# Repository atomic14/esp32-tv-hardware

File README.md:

# WIP - ESP32-TV Hardware Files

This is Work In Progress - I'm still working on this.

This repo contains/will contain the hardware design files for the ESP32-TV project.

## Schematic

You can either open this up in KiCad, or there's a PDF [here](./images/micro-esp32-s3.pdf).

## PCB

Open this up in KiCad to export the Gerber files.

## What's this all about?

More details to follow...

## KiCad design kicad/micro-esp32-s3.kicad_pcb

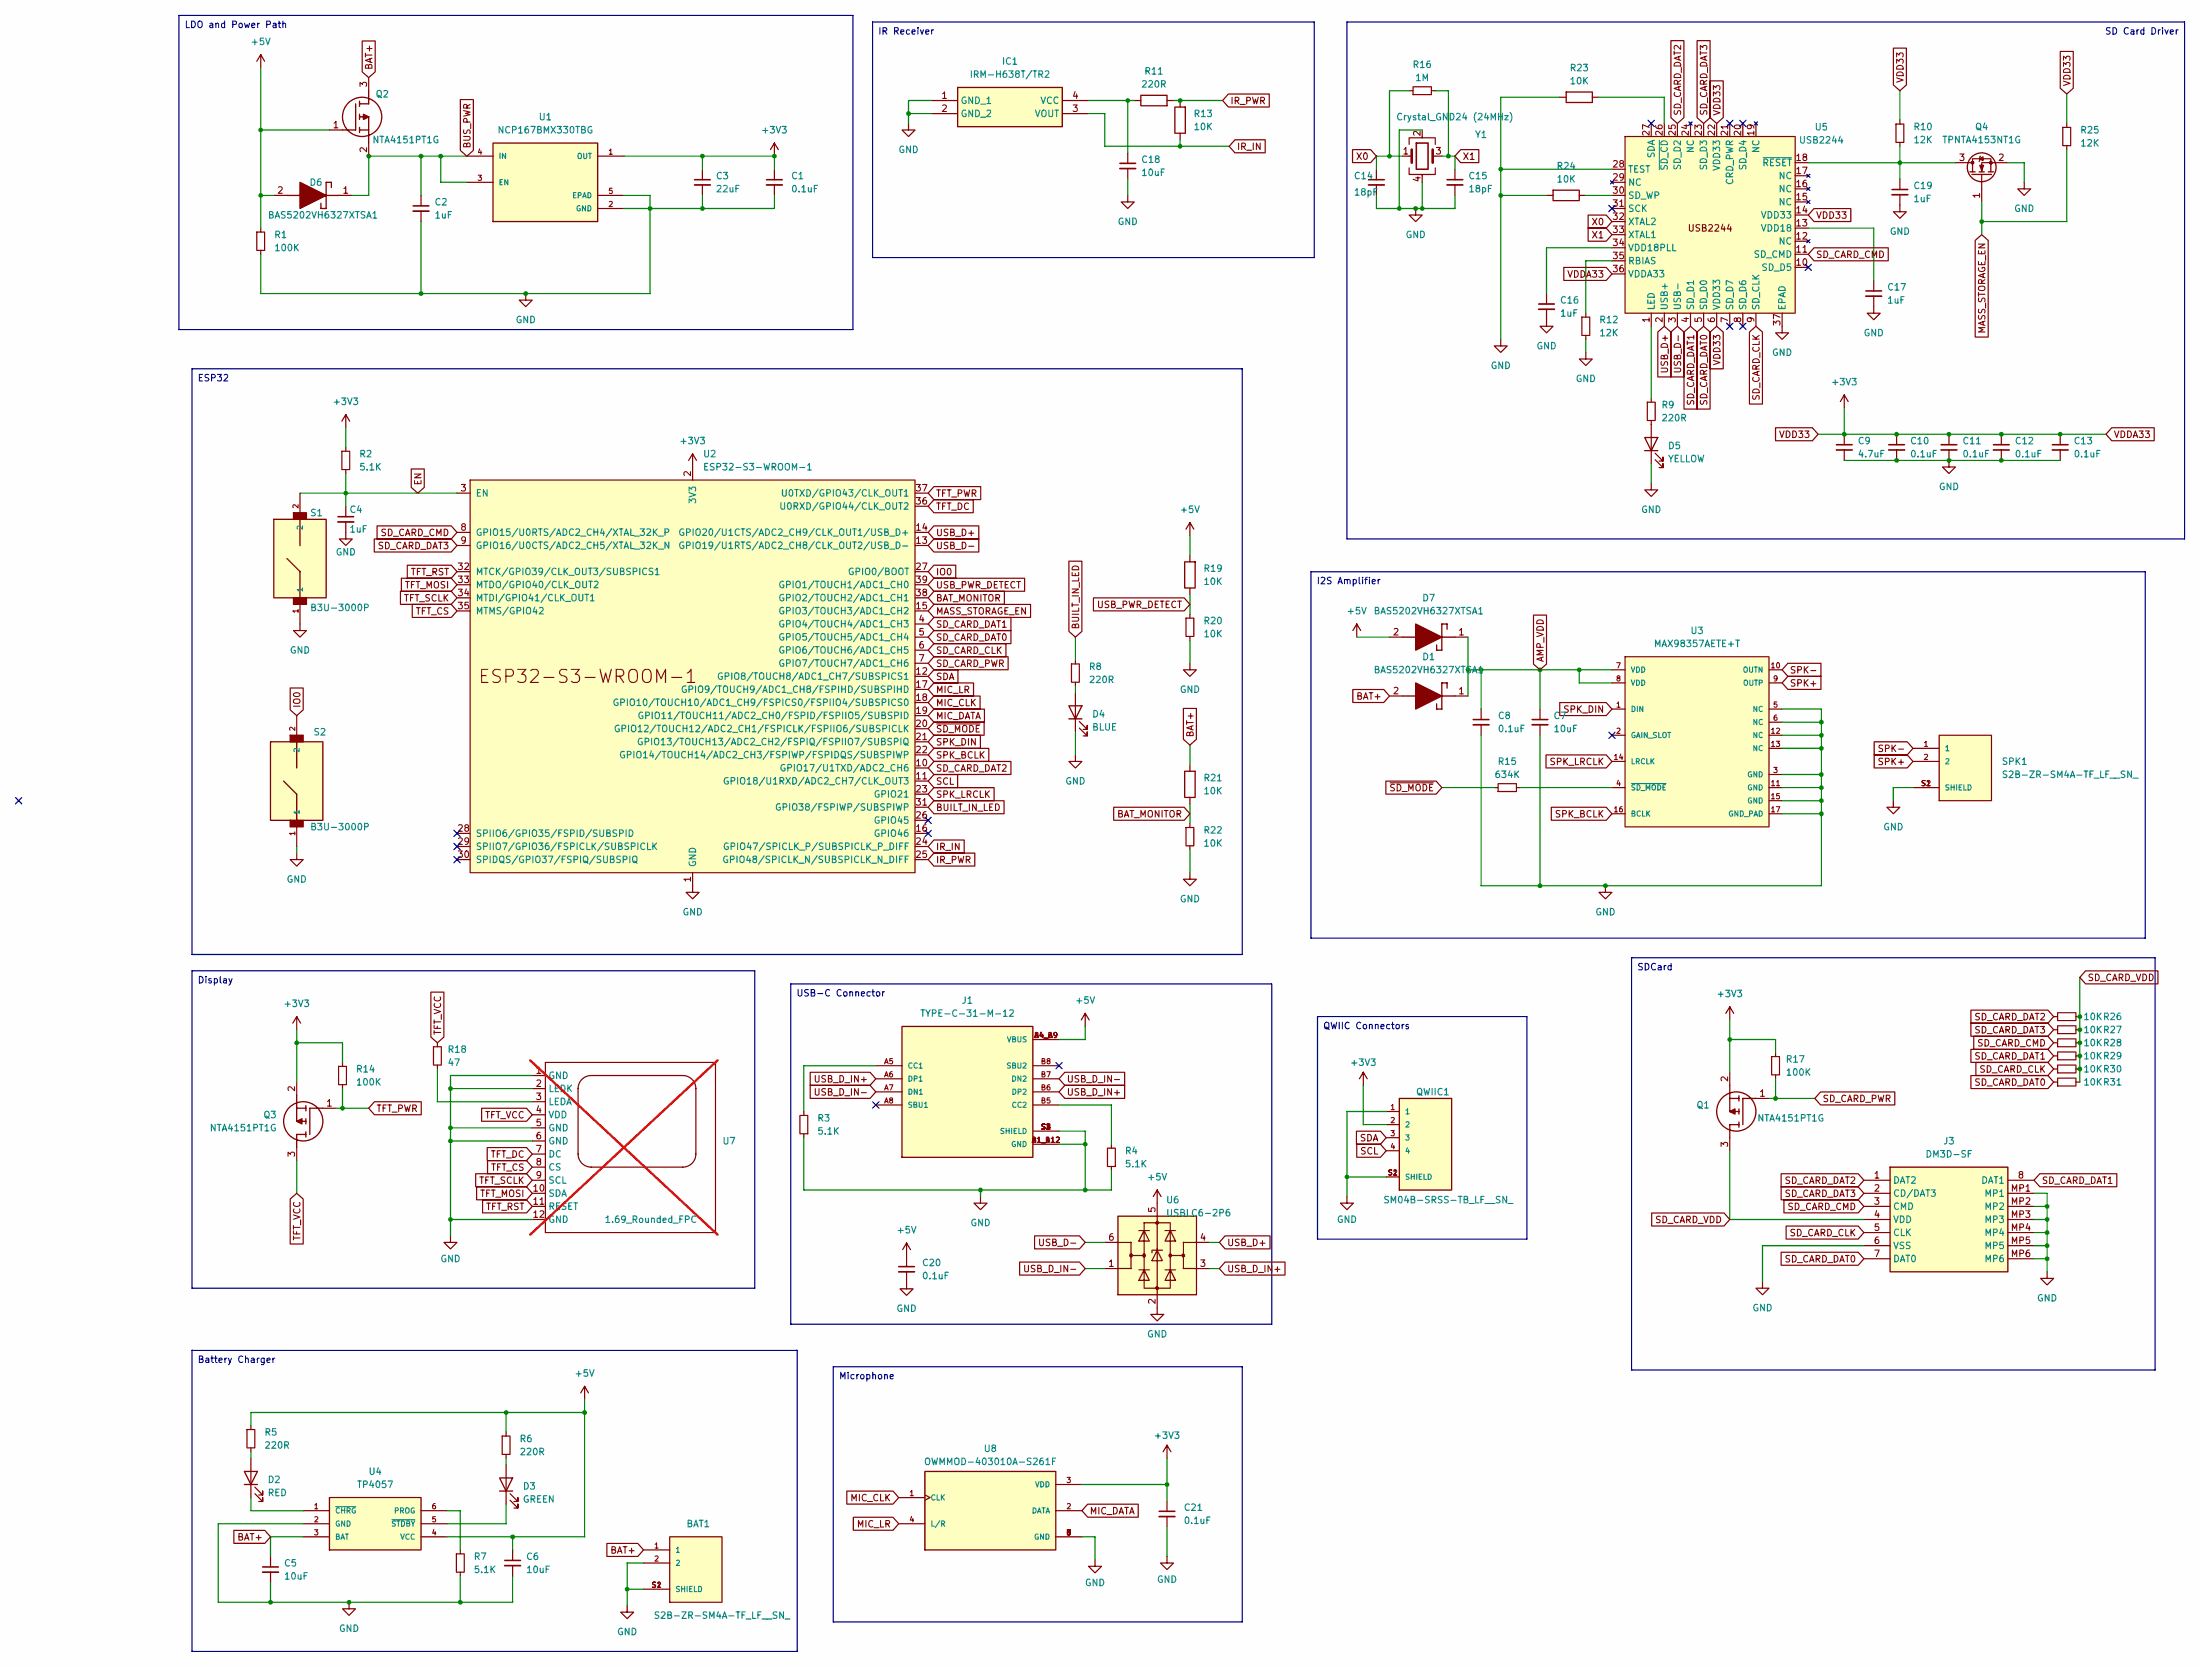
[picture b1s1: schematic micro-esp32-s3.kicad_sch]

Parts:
BAT1: S2B-ZR-SM4A-TF_LF__SN_; JST_S2B-ZR-SM4A-TF_LF__SN_; PARTREV N/A
C1, C8, C10, C11, C12, C13, C20, C21: 0.1uF; C_0402_1005Metric
C2: 1uF; C_0402_1005Metric; Mfg Part # test
C3: 22uF; C_0402_1005Metric
C4, C16, C17, C19: 1uF; C_0402_1005Metric
C5, C6, C7, C18: 10uF; C_0402_1005Metric
C9: 4.7uF; C_0402_1005Metric
C14, C15: 18pF; C_0402_1005Metric
D1, D6, D7: BAS5202VH6327XTSA1; SODFL1608X59N; Manufacturer_Part_Number BAS5202VH6327XTSA1; Mouser Part Number 726-BAS5202VH6327XTS
D2: RED; LED_0402_1005Metric
D3: GREEN; LED_0402_1005Metric
D4: BLUE; LED_0402_1005Metric
D5: YELLOW; LED_0402_1005Metric
IC1: IRM-H638T/TR2; SOP254P700X405-4N; Manufacturer_Part_Number IRM-H638M3/TR2
J1: TYPE-C-31-M-12; HRO_TYPE-C-31-M-12; PARTREV 2020.12.08
J3: DM3D-SF; DM3DSF; Manufacturer_Part_Number DM3D-SF; Mouser Part Number 798-DM3D-SF
Q1, Q2, Q3: NTA4151PT1G; SOT50P160X90-3N; Manufacturer_Part_Number NTA4151PT1G; Mouser Part Number 863-NTA4151PT1G
Q4: TPNTA4153NT1G; SOT-523
QWIIC1: SM04B-SRSS-TB_LF__SN_; JST_SM04B-SRSS-TB_LF__SN_
R1, R14, R17: 100K; R_0402_1005Metric
R2, R3, R4, R7: 5.1K; R_0402_1005Metric
R5, R6, R8, R9, R11: 220R; R_0402_1005Metric
R10, R12, R25: 12K; R_0402_1005Metric
R13, R19, R20, R21, R22, R23, R24, R26, R27, R28, R29, R30, R31: 10K; R_0402_1005Metric
R15: 634K; R_0402_1005Metric
R16: 1M; R_0402_1005Metric
R18: 47; R_0402_1005Metric
S1, S2: B3U-3000P; SW_B3U-3000P
SPK1: S2B-ZR-SM4A-TF_LF__SN_; JST_S2B-ZR-SM4A-TF_LF__SN_; PARTREV N/A
U1: NCP167BMX330TBG; VREG_NCP167BMX330TBG; PARTREV 5
U2: ESP32-S3-WROOM-1; ESP32-S3-WROOM-1U
U3: MAX98357AETE+T; Maxim_Electronics-21-0896-0-0-0; mouser part number 700-MAX98357AETE+T; digikey description Amplifier IC 2-Channel (Stereo) Class D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
U4: TP4057; SOT-23-6
U5: USB2244; QFN-36-1EP_6x6mm_P0.5mm_EP4.1x4.1mm
U6: USBLC6-2P6; SOT-666
U7: 1.69_Rounded_FPC; fpc_12_pin_0.7_pitch; not fitted
U8: OWMMOD-403010A-S261F; MIC_OWMMOD-403010A-S261F; PARTREV 00; DigiKey_Part_Number 3949-OWMMOD-403010A-S261F-ND
Y1: Crystal_GND24 (24MHz); Crystal_SMD_3225-4Pin_3.2x2.5mm

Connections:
+5V: C6.1, C20.1, D6.2 (A), D7.2 (A), J1.A4_B9 (VBUS), J1.B4_A9 (VBUS), Q2.1 (G), R1.1, R5.1, R6.1, R19.2, U4.4 (VCC), U6.5 (VBUS)
AMP_VDD: C7.1, C8.1, D1.1 (K), D7.1 (K), U3.7 (VDD), U3.8 (VDD)
BAT+: BAT1.1, C5.1, D1.2 (A), Q2.3 (D), R21.2, U4.3 (BAT)
BAT_MONITOR: R21.1, R22.1, U2.38 (GPIO2/TOUCH2/ADC1_CH1)
BUILT_IN_LED: R8.1, U2.31 (GPIO38/FSPIWP/SUBSPIWP)
BUS_PWR: C2.1, D6.1 (K), Q2.2 (S), U1.3 (EN), U1.4 (IN)
EN: C4.1, R2.2, S1.2, U2.3 (EN)
GND: BAT1.2, BAT1.S1 (SHIELD), BAT1.S2 (SHIELD), C1.2, C2.2, C3.2, C4.2, C5.2, C6.2, C7.2, C8.2, C9.2, C10.2, C11.2, C12.2, C13.2, C14.2, C15.2, C16.2, C17.2, C18.2, C19.2, C20.2, C21.2, D4.1 (K), D5.1 (K), IC1.1 (GND_1), IC1.2 (GND_2), J1.A1_B12 (GND), J1.B1_A12 (GND), J1.S1 (SHIELD), J1.S2 (SHIELD), J1.S3 (SHIELD), J1.S4 (SHIELD), J3.6 (VSS), J3.MP1, J3.MP2, J3.MP3, J3.MP4, J3.MP5, J3.MP6, Q4.2 (S), QWIIC1.1, QWIIC1.S1 (SHIELD), QWIIC1.S2 (SHIELD), R1.2, R3.1, R4.1, R7.2, R12.2, R20.2, R22.2, R23.2, R24.2, S1.1, S2.1, SPK1.S1 (SHIELD), SPK1.S2 (SHIELD), U1.2 (GND), U1.5 (EPAD), U2.1 (GND), U2.40 (GND), U2.41 (GND), U3.3 (GND), U3.5 (NC), U3.6 (NC), U3.11 (GND), U3.12 (NC), U3.13 (NC), U3.15 (GND), U3.17 (GND_PAD), U4.2 (GND), U5.28 (TEST), U5.37 (EPAD), U6.2 (GND), U7.1 (GND), U7.2 (LEDK), U7.5 (GND), U7.6 (GND), U7.12 (GND), U8.5 (GND), U8.6 (GND), U8.7 (GND), U8.8 (GND), Y1.2, Y1.4
IO0: S2.2, U2.27 (GPIO0/BOOT)
IR_IN: IC1.3 (VOUT), R13.1, U2.24 (GPIO47/SPICLK_P/SUBSPICLK_P_DIFF)
IR_PWR: R11.2, R13.2, U2.25 (GPIO48/SPICLK_N/SUBSPICLK_N_DIFF)
MASS_STORAGE_EN: Q4.1 (G), R25.2, U2.15 (GPIO3/TOUCH3/ADC1_CH2)
MIC_CLK: U2.18 (GPIO10/TOUCH10/ADC1_CH9/FSPICS0/FSPIIO4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), U8.1 (CLK)
MIC_DATA: U2.19 (GPIO11/TOUCH11/ADC2_CH0/FSPID/FSPIIO5/S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), U8.2 (DATA)
MIC_LR: U2.17 (GPIO9/TOUCH9/ADC1_CH8/FSPIHD/SUBSPIHD), U8.4 (L/R)
unnamed: D2.2 (A), R5.2
unnamed: D2.1 (K), U4.1 (~CHRG)
unnamed: D3.2 (A), R6.2
unnamed: D3.1 (K), U4.5 (~STDBY)
unnamed: D4.2 (A), R8.2
unnamed: D5.2 (A), R9.2
unnamed: C18.1, IC1.4 (VCC), R11.1
unnamed: J1.A5 (CC1), R3.2
unnamed: J1.B5 (CC2), R4.2
unnamed: C19.1, Q4.3 (D), R10.2, U5.18 (~RESET)
unnamed: R15.2, U3.4 (~SD_MODE)
unnamed: R7.1, U4.6 (PROG)
unnamed: R9.1, U5.1 (LED)
unnamed: R12.1, U5.35 (RBIAS)
unnamed: R24.1, U5.30 (SD_WP)
unnamed: C17.1, U5.13 (VDD18)
unnamed: C16.1, U5.34 (VDD18PLL)
unnamed: R23.1, U5.26 (~SD_CD)
unnamed: R18.2, U7.3 (LEDA)
SCL: QWIIC1.4, U2.11 (GPIO18/U1RXD/ADC2_CH7/CLK_OUT3)
SDA: QWIIC1.3, U2.12 (GPIO8/TOUCH8/ADC1_CH7/SUBSPICS1)
SD_CARD_CLK: J3.5 (CLK), R30.1, U2.6 (GPIO6/TOUCH6/ADC1_CH5), U5.9 (SD_CLK)
SD_CARD_CMD: J3.3 (CMD), R28.1, U2.8 (GPIO15/U0RTS/ADC2_CH4/XTAL_32K_P), U5.11 (SD_CMD)
SD_CARD_DAT0: J3.7 (DAT0), R31.1, U2.5 (GPIO5/TOUCH5/ADC1_CH4), U5.5 (SD_D0)
SD_CARD_DAT1: J3.8 (DAT1), R29.1, U2.4 (GPIO4/TOUCH4/ADC1_CH3), U5.4 (SD_D1)
SD_CARD_DAT2: J3.1 (DAT2), R26.1, U2.10 (GPIO17/U1TXD/ADC2_CH6), U5.25 (SD_D2)
SD_CARD_DAT3: J3.2 (CD/DAT3), R27.1, U2.9 (GPIO16/U0CTS/ADC2_CH5/XTAL_32K_N), U5.23 (SD_D3)
SD_CARD_PWR: Q1.1 (G), R17.2, U2.7 (GPIO7/TOUCH7/ADC1_CH6)
SD_CARD_VDD: J3.4 (VDD), Q1.3 (D), R26.2, R27.2, R28.2, R29.2, R30.2, R31.2
SPK+: SPK1.2, U3.9 (OUTP)
SPK-: SPK1.1, U3.10 (OUTN)
SPK_BCLK: U2.22 (GPIO14/TOUCH14/ADC2_CH3/FSPIWP/FSPIDQS/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), U3.16 (BCLK)
SPK_DIN: U2.21 (GPIO13/TOUCH13/ADC2_CH2/FSPIQ/FSPIIO7/S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), U3.1 (DIN)
SPK_LRCLK: U2.23 (GPIO21), U3.14 (LRCLK)
TFT_CS: U2.35 (MTMS/GPIO42), U7.8 (CS)
TFT_DC: U2.36 (U0RXD/GPIO44/CLK_OUT2), U7.7 (DC)
TFT_MOSI: U2.33 (MTDO/GPIO40/CLK_OUT2), U7.10 (SDA)
TFT_PWR: Q3.1 (G), R14.2, U2.37 (U0TXD/GPIO43/CLK_OUT1)
TFT_RST: U2.32 (MTCK/GPIO39/CLK_OUT3/SUBSPICS1), U7.11 (RESET)
TFT_SCLK: U2.34 (MTDI/GPIO41/CLK_OUT1), U7.9 (SCL)
TFT_VCC: Q3.3 (D), R18.1, U7.4 (VDD)
USB_D+: U2.14 (GPIO20/U1CTS/ADC2_CH9/CLK_OUT1/USB_D+), U5.2 (USB+), U6.4 (I/O2)
USB_D-: U2.13 (GPIO19/U1RTS/ADC2_CH8/CLK_OUT2/USB_D-), U5.3 (USB-), U6.6 (I/O1)
USB_D_IN+: J1.A6 (DP1), J1.B6 (DP2), U6.3 (I/O2)
USB_D_IN-: J1.A7 (DN1), J1.B7 (DN2), U6.1 (I/O1)
USB_PWR_DETECT: R19.1, R20.1, U2.39 (GPIO1/TOUCH1/ADC1_CH0)
VDD33: C1.1, C3.1, C9.1, C10.1, C11.1, C12.1, C13.1, C21.1, Q1.2 (S), Q3.2 (S), QWIIC1.2, R2.1, R10.1, R14.1, R17.1, R25.1, U1.1 (OUT), U2.2 (3V3), U5.6 (VDD33), U5.14 (VDD33), U5.22 (VDD33), U5.36 (VDDA33), U8.3 (VDD)
X0: C14.1, R16.1, U5.32 (XTAL2), Y1.1
X1: C15.1, R16.2, U5.33 (XTAL1), Y1.3
~SD_MODE: R15.1, U2.20 (GPIO12/TOUCH12/ADC2_CH1/FSPICLK/FSPIIO6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)

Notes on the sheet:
QWIIC Connectors
Microphone
SDCard
Battery Charger
SD Card Driver
IR Receiver
ESP32
Display
USB-C Connector
I2S Amplifier
LDO and Power Path

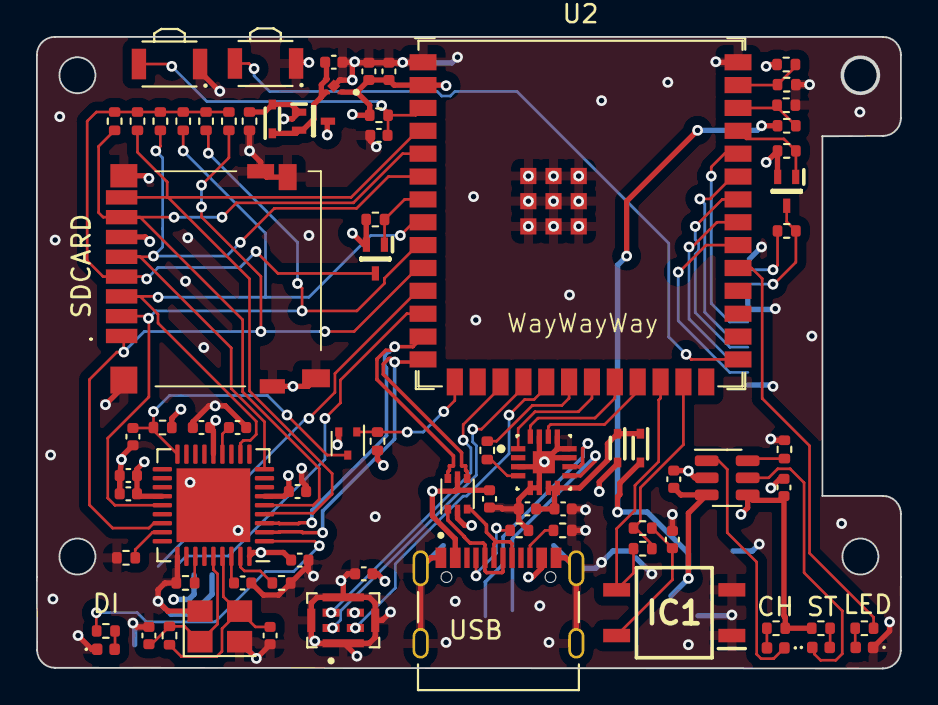
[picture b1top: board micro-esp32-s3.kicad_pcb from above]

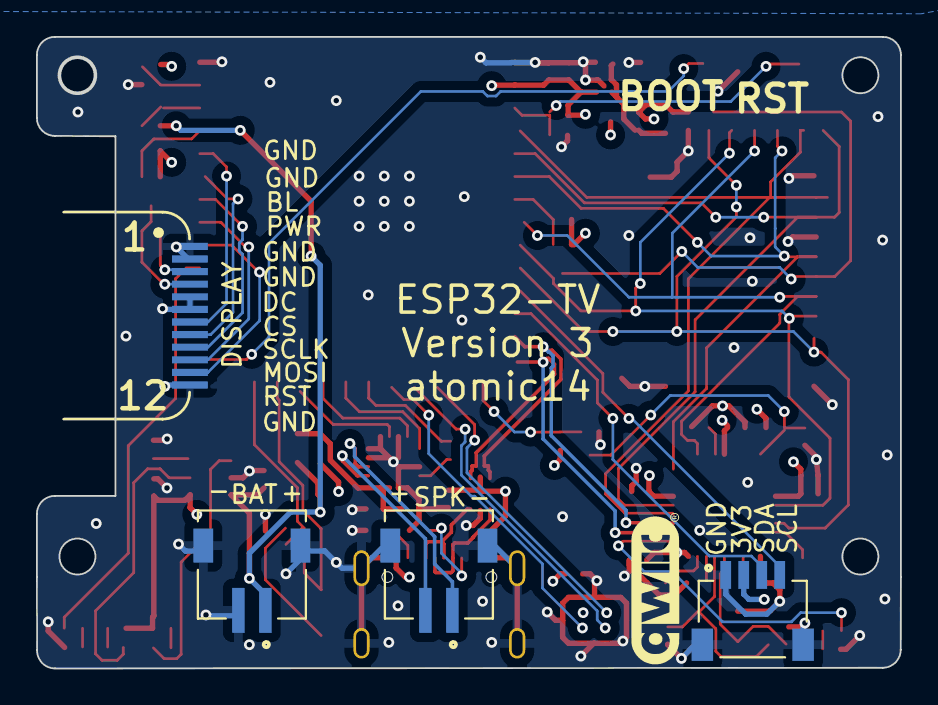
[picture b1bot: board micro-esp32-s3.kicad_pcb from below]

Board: 4 copper layers, 48.0 x 35.1 mm, 80 parts (4 on the bottom side), 65 nets.

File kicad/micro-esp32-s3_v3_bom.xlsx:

Item # | *Designator | *Qty | Manufacturer | *Mfg Part # | Description / Value | *Package/Footprint | Mounting Type | Your Instructions / Notes
1 | R31,R30,R29,R28,R27,R26,R20,R13,R24,R19,R22,R23,R21 | 13 | KOA Speer | SG73P1EWTTP1002F | 10K | R_0402_1005Metric | SMD
2 | S2,S1 | 2 | Omron Electronics | B3U-3000P | B3U-3000P | SW_B3U-3000P | SMD
3 | C1,C20,C8,C10,C13,C11,C12,C21 | 8 | YAGEO | CC0402KRX5R6BB104 | 100nF | C_0402_1005Metric | SMD
4 | R3,R7,R4,R2 | 4 | RALEC | RTT02512JTH | 5.1K | R_0402_1005Metric | SMD
5 | U8 | 1 | OLEWOLFF | OWMMOD-403010A-S261F | OWMMOD-403010A-S261F | OWMMOD-403010A-S261F | SMD | NOTE - this is the top ported version - OWMMOD-403010A-S261F - https://mm.digik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
6 | C17,C19,C2,C16,C4 | 5 | CCTC | TCC0402X5R105K100AT | 1uF | C_0402_1005Metric | SMD
7 | U6 | 1 | TECH PUBLIC | USBLC6-2P6 | USBLC6-2P6 | SOT-666-6 | SMD
8 | D7,D6,D1 | 3 | Infineon | BAS 52-02V H6327 | BAS5202VH6327XTSA1 | SODFL1608X59N | SMD
9 | C5,C6,C18,C7 | 4 | SAMSUNG | CL05A106MP5NUNC | 10uF | C_0402_1005Metric | SMD
10 | R15 | 1 | YAGEO | AF0402FR-07634KL | 634K | R_0402_1005Metric | SMD
11 | IC1 | 1 | Everlight | IRM-H638T/TR2 | IRM-H638T/TR2 | SOP254P700X405-4N | SMD
12 | Q1,Q3,Q2 | 3 | onsemi | NTA4151PT1G | NTA4151PT1G | SOT50P160X90-3N | SMD
13 | U1 | 1 | onsemi | NCP167BMX330TBG | NCP167BMX330TBG | VREG_NCP167BMX330TBG | SMD
14 | R1,R14,R17 | 3 | KOA Speer | SG73P1EWTTP1003F | 100K | R_0402_1005Metric | SMD
15 | D5 | 1 | Everlight Elec | 16-213UYC/S530-A2/TR8 | YELLOW LED | LED_0402_1005Metric | SMD | Any 0402 Yellow LED
16 | R18 | 1 | KOA Speer | RK73H1ERTTP39R0F | 39 | R_0402_1005Metric | SMD
17 | R12,R10,R25 | 3 | KOA Speer | SG73P1EWTTP1202F | 12K | R_0402_1005Metric | SMD
18 | U4 | 1 | TOPPOWER | TP4057-42-SOT26-R | TP4057 | SOT-23-6 | SMD
19 | U2 | 1 | Espressif Systems | ESP32-S3-WROOM-1U-N8R8 | ESP32-S3-WROOM-1 | ESP32-S3-WROOM-1U | SMD
20 | Q4 | 1 | TECH PUBLIC | TPNTA4153NT1G | TPNTA4153NT1G | SOT-523-3 | SMD
21 | C3 | 1 | muRata | GRM155R60J226ME11D | 22uF | C_0402_1005Metric | SMD
22 | C14,C15 | 2 | Kyocera AVX | 0402ZK180FBWTR | 18pF | C_0402_1005Metric | SMD
23 | U5 | 1 | Microchip | USB2240-AEZG-06 | USB2240 | QFN-36-EP(6x6) | SMD
24 | R5,R9,R6,R8,R11 | 5 | KOA Speer | SG73P1EWTTP221G | 220R | R_0402_1005Metric | SMD
25 | Y1 | 1 | JWT | CF4024M00012 | Crystal_GND24 (24MHz) | Crystal_SMD_3225-4Pin_3.2x2.5mm | SMD
26 | C9 | 1 | Samsung Electro-Mechanics | CL05A475MP5NRNC | 4.7uF | C_0402_1005Metric | SMD
27 | J3 | 1 | Hirose | DM3D-SF | DM3D-SF | DM3DSF | SMD
28 | D2 | 1 | Everlight Elec | 16-213/R6C-AQ2R2B/3T | RED LED | LED_0402_1005Metric | SMD | Any 0402 Red LED
29 | D3 | 1 | Everlight Elec | 16-213/BHC-AN1P2/3T | BLUE LED | LED_0402_1005Metric | SMD | Any 0402 Blue LED
30 | R16 | 1 | KOA Speer | SG73P1EWTTP1004F | 1M | R_0402_1005Metric | SMD
31 | U3 | 1 | MAXIM | MAX98357AETE+T | MAX98357AETE+T | TQFN-16_L3.0-W3.0-P0.50-BL-EP1.5 | SMD
32 | J1 | 1 | 韩国韩荣 | TYPE-C-31-M-12 | TYPE-C-31-M-12 | USB-C_SMD-TYPE-C-31-M-12 | SMD
33 | D3 | 1 | Everlight Elec | 16-213/GHC-YR1S1/3T | GREEN LED | LED_0402_1005Metric | SMD | Any 0402 Green LED
34 | SPK1,BAT1 | 2 | JST | S2B-ZR-SM4A-TF | S2B-ZR-SM4A-TF_LF__SN_ | S2B-ZR-SM4A-TF | SMD
35 | QWIIC1 | 1 | JST | SM04B-SRSS-TB | SM04B-SRSS-TB_LF__SN_ | SM04B-SRSS-TB | SMD

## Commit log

2023-11-14 Change pull down resistor on mass storage enable to 1K
2023-11-17 Clean up schematic
2023-11-17 Fix power path in schematic
2023-11-17 Fix diode position
2023-11-17 Update PCB screenshot
2023-12-04 Make sure GPIO45 and GPIO46 are disconnected
2023-12-08 WIP - version 3
2023-12-08 V3 Work in progress
2023-12-09 Version 3 - Ready for review
2023-12-09 Removes extra "."
2023-12-10 Submitted Version
2023-12-10 Updates images
